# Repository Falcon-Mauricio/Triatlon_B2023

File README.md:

# Triatlon_B2023

### Indice
[PINOUT PCB](#pinout)<br>
[Normas de convivencia de codigo](#normas)<br>
[Organizacion del repositorio y colaboracion](#colab)<br>
[Imagenes](#imag)<br>

## PINOUT PCB

### Kairimi
```
// Motores
#define M2A 22
#define M2B 23
#define M1B 19
#define M1A 21

// Sensores
#define SENSOR_1 13
#define SENSOR_2 27
#define SENSOR_3 26
#define SENSOR_4 25
#define SENSOR_5 34
#define SENSOR_6 35
#define SENSOR_7 32
#define SENSOR_8 33
#define LEFT_CNY 27
#define RIGHT_CNY 25
#define BACK_CNY 26

// Control
#define BUZZER 18
#define PUSH_1 16
#define PUSH_2 17
```

### C5
```
#define SENSOR_1 13 // left side sharp  
#define SENSOR_2 27 // back cny
#define SENSOR_3 26 // right side sharp
#define SENSOR_4 25 // right cny
#define SENSOR_5 34 // left cny
#define SENSOR_6 35 // left sharp
#define SENSOR_7 32 // center sharp
#define SENSOR_8 33 // right sharp

```
<br>

## Normas de convivencia de codigo

* #### 1.  Convencion de nomenclatura:

    | Tipo      | Caso           | Ejemplo      |
    | :-------: |:--------------:|:------------:|
    | constantes| screaming snake|MAX_READING   |
    | variables | snake case     |color_deadline|
    | objetos   | snake case     |left_sharp    |
    | clases    | pascal case    |Motor         |
    | funciones | pascal case    |ReadFloor     |

* #### 2.  Orden del codigo:

    * Importar librerias
    * Definicion pines
    * Definicion de constantes / variables globales
    * Creacion de clases / objetos (hasta terminar la modularizacion)
    * Funciones globales
    * Velocista
    * Sumo radiocontrolado
    * Despejar area
    * Seleccion de modo / setup / loop
    
* #### 3. Legibilidad:

    * Usar define para los numeros aislados
    * Comentarios descriptivos
    * Codigo limpio y ordenado

<br>

## Organizacion del repositorio y colaboracion

### Arbol de carpetas:

```
├───C5
│   ├───3D
│   ├───CODE
│   └───PCB
├───Kairimi
│   ├───3D
│   ├───CODE
│   └───PCB
├───resources
└───shared
    ├───examples
    └───libs
```

* C5: Dedicado a la version C5 (Rodri/Mauri)

* Kairimi: Dedicado a la version Kairimi (Iris/Julian).
* resources: Librerias externas necesarias para correr el codigo
* shared: Archivos compartidos para los dos robots, como librerias dedicadas

### Colaboracion:

Para colaborar es preferible forkear el repositorio, editar lo necesario en el momento y enviar un pull request. Esto para mantener la actualizacion de archivos ordenada y evitar conflictos entre los robots.

Cuando se alcance una version funcional del robot tagerla marcando las diferencias y mejoras respecto a la anterior y tiempos records de pistas.

<br>

## Imagenes 3Ds / PCBs

### KAIRIMI:

### C5:

3d en desarrollo.

# Manolos ahi voy 🤤

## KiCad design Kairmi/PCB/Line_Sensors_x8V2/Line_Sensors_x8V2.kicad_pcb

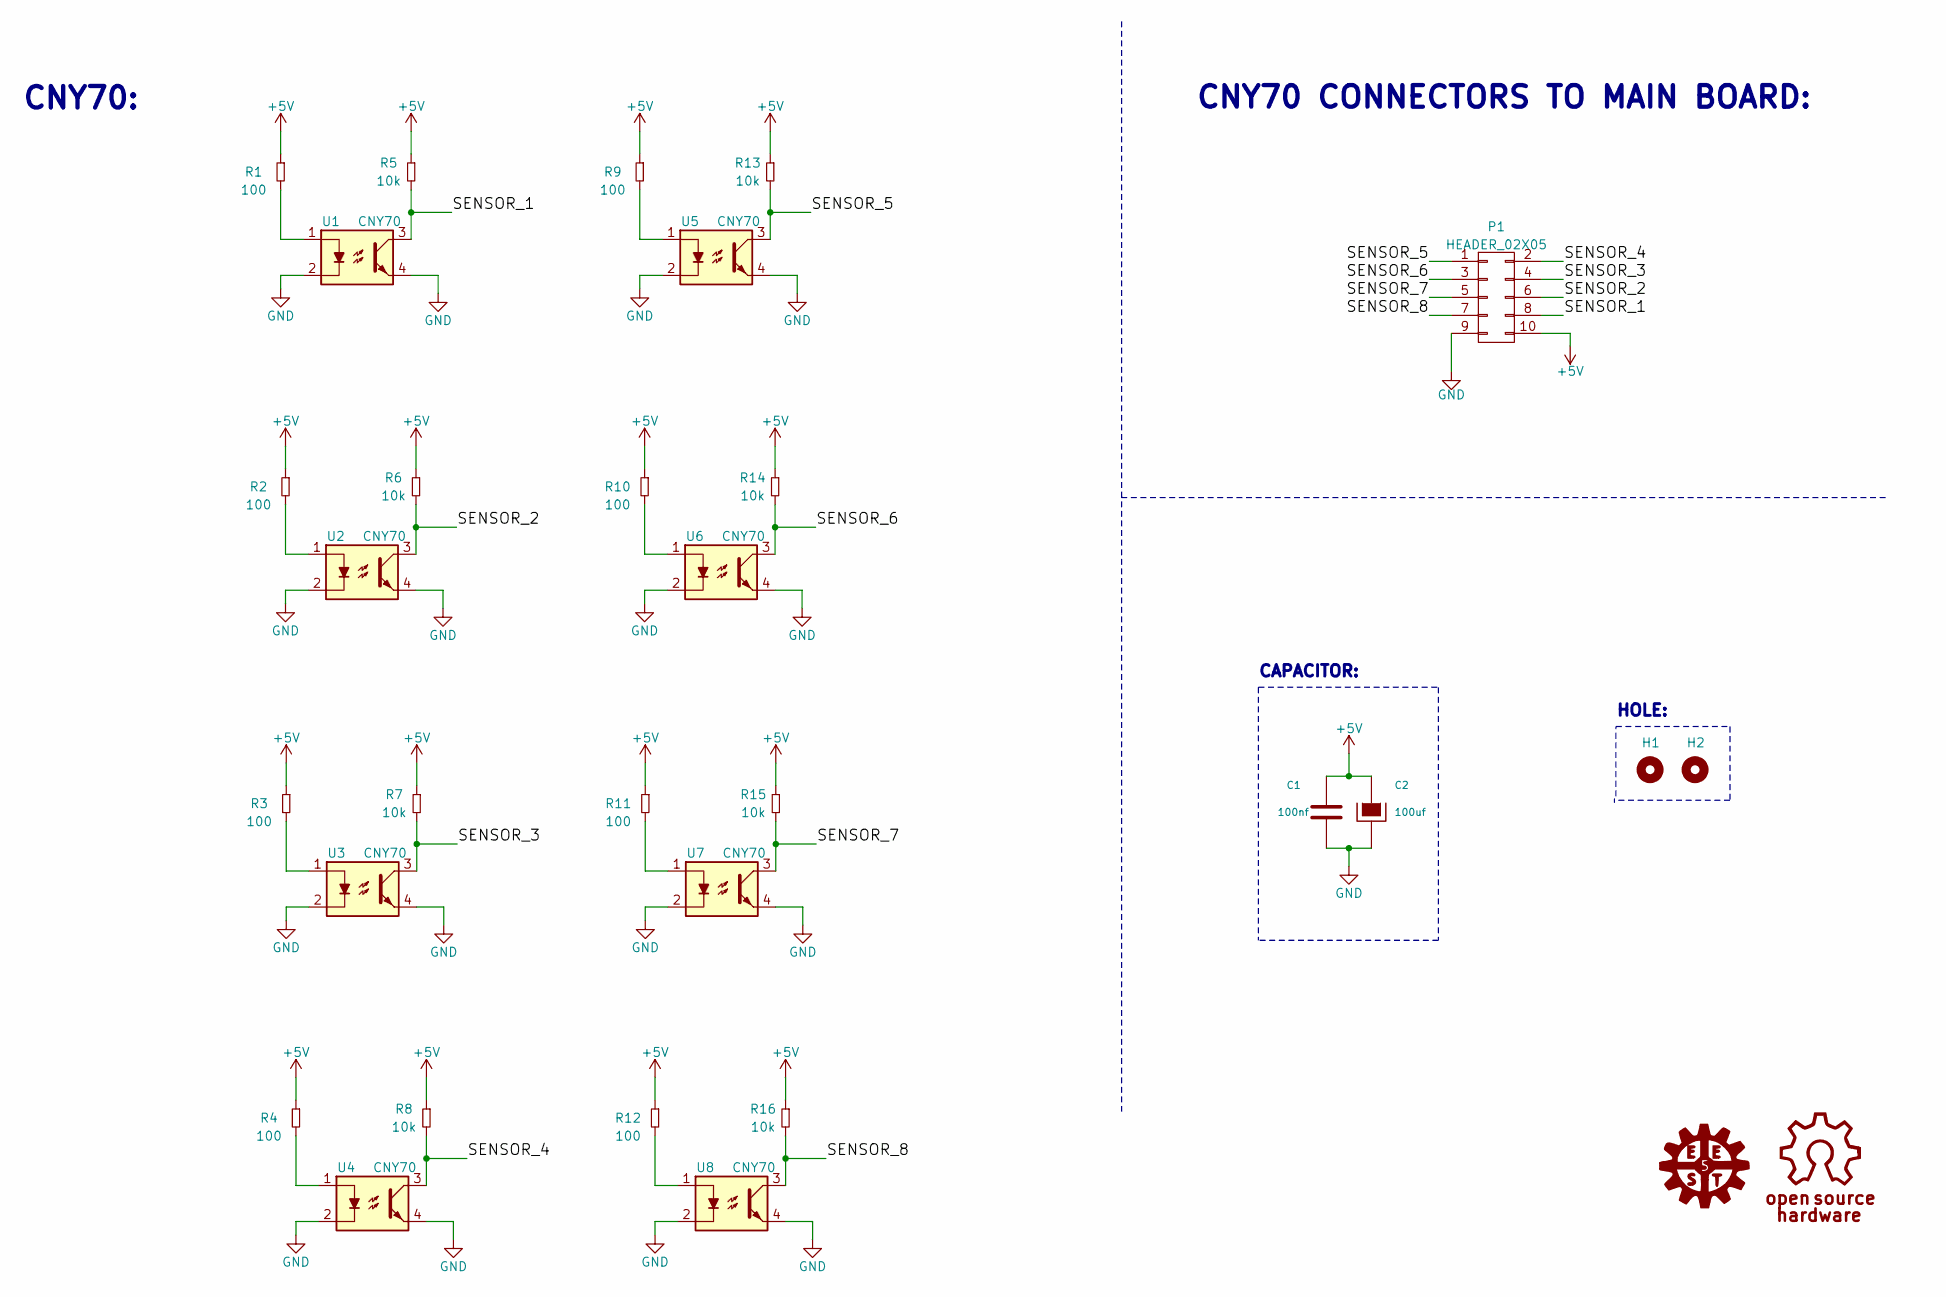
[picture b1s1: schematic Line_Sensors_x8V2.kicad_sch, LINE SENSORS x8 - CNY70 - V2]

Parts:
C1: 100nf; C_0805_2012Metric_Pad1.18x1.45mm_HandSolder
C2: 100uf; C_Radial_D5.0mm_H11.0mm_P2.00mm
H1, H2: HOLE; Separador_M3_5mm
P1: HEADER_02X05; Header_2x05x2.54mm_Vertical
R1, R2, R3, R4, R9, R10, R11, R12: 100; R_1206
R5, R6, R7, R8, R13, R14, R15, R16: 10k; R_1206
U1, U2, U3, U4, U5, U6, U7, U8: CNY70

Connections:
+5V: C1.1, C2.1, P1.10, R1.1, R2.1, R3.1, R4.1, R5.1, R6.1, R7.1, R8.1, R9.1, R10.1, R11.1, R12.1, R13.1, R14.1, R15.1, R16.1
/SENSOR_1: P1.8, R5.2, U1.3
/SENSOR_2: P1.6, R6.2, U2.3
/SENSOR_3: P1.4, R7.2, U3.3
/SENSOR_4: P1.2, R8.2, U4.3
/SENSOR_5: P1.1, R13.2, U5.3
/SENSOR_6: P1.3, R14.2, U6.3
/SENSOR_7: P1.5, R15.2, U7.3
/SENSOR_8: P1.7, R16.2, U8.3
GND: C1.2, C2.2, P1.9, U1.2, U1.4, U2.2, U2.4, U3.2, U3.4, U4.2, U4.4, U5.2, U5.4, U6.2, U6.4, U7.2, U7.4, U8.2, U8.4
unnamed: R1.2, U1.1
unnamed: R2.2, U2.1
unnamed: R3.2, U3.1
unnamed: R4.2, U4.1
unnamed: R9.2, U5.1
unnamed: R10.2, U6.1
unnamed: R11.2, U7.1
unnamed: R12.2, U8.1

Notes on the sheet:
CNY70 CONNECTORS TO MAIN BOARD:
CAPACITOR:
CNY70:
HOLE:

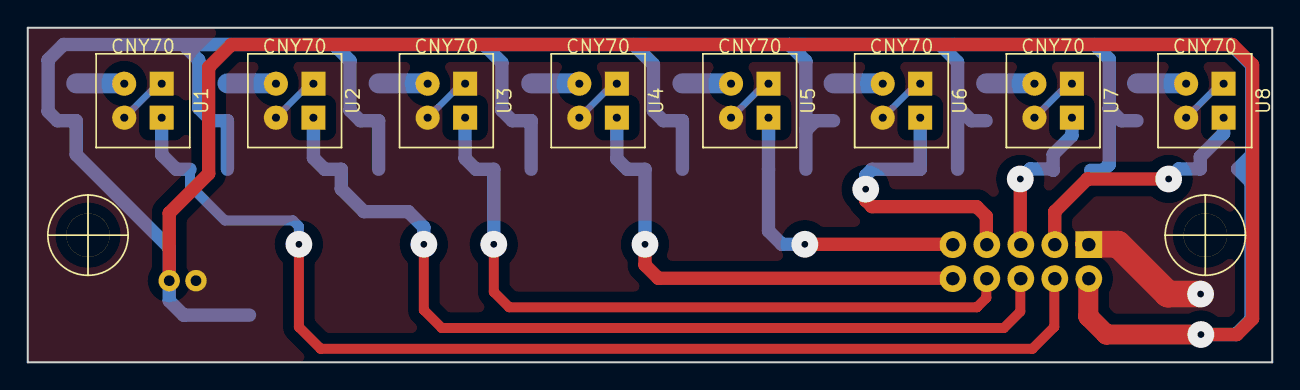
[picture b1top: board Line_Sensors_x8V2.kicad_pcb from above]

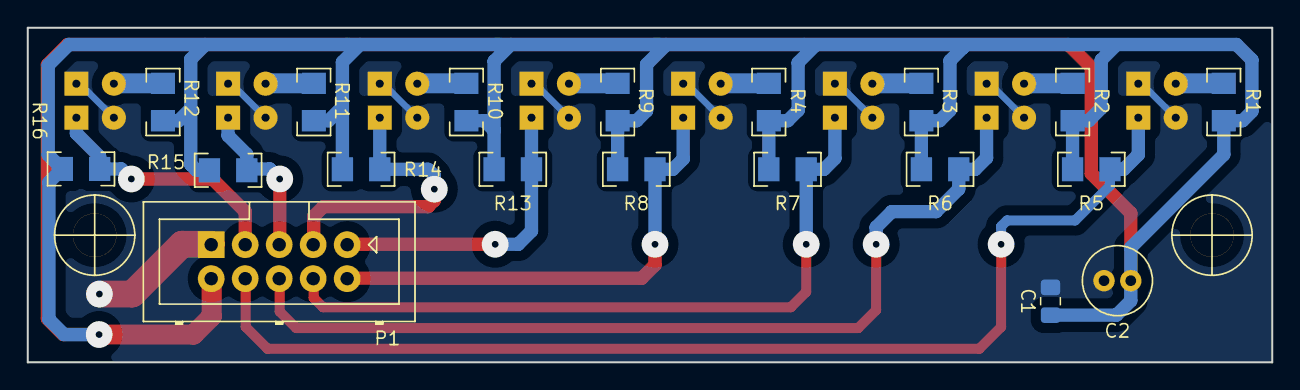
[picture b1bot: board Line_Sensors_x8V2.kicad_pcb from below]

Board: 2 copper layers, 93.0 x 25.0 mm, 29 parts (21 on the bottom side), 18 nets.

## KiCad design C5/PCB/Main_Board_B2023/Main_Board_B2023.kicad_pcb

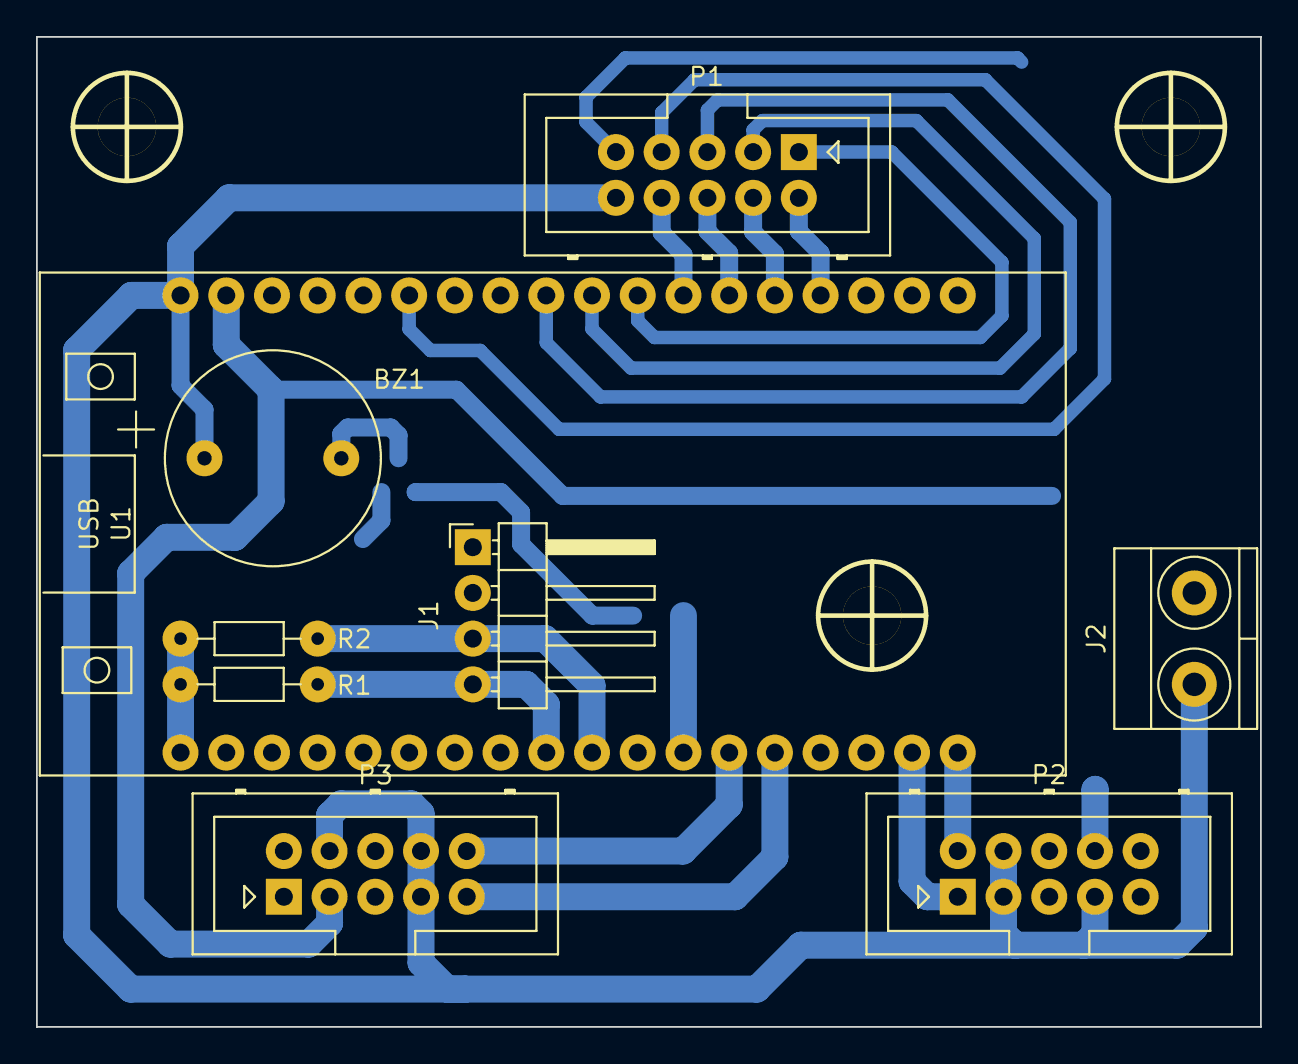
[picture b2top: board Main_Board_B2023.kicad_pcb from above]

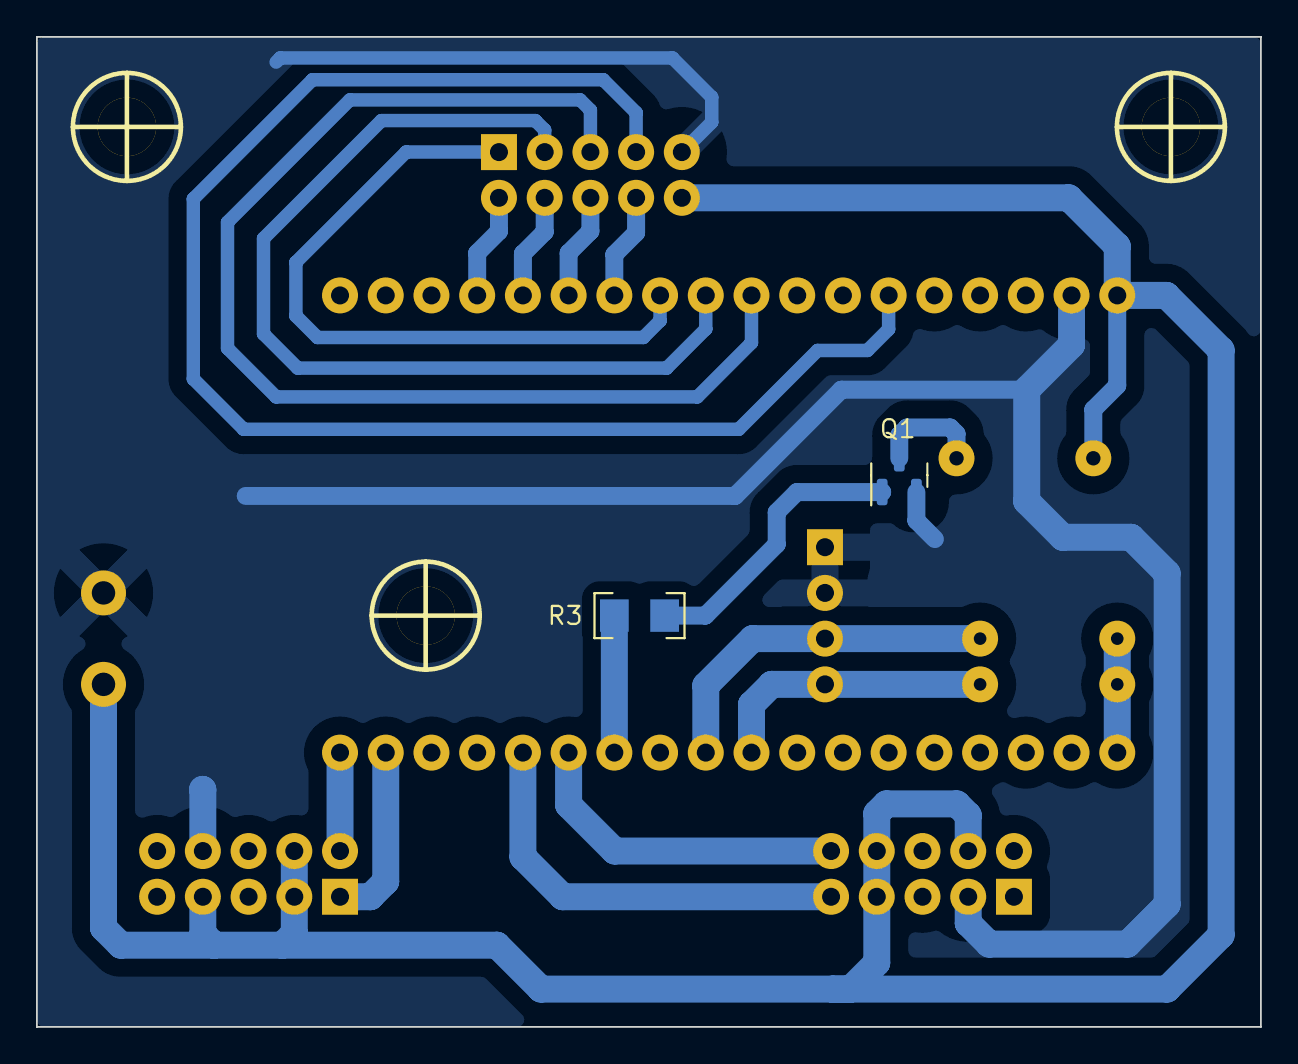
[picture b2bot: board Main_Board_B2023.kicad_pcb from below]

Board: 2 copper layers, 68.0 x 55.0 mm, 14 parts (2 on the bottom side), 20 nets.

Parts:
BZ1: Buzzer; Buzzer_12mm
H1, H2, H3: Mounting_Hole; Separador_M3_5mm
J1: Conn_01x04_Pin; PinHeader_1x04_P2.54mm_Horizontal
J2: TB_1X2; BORNERA2_AZUL
P1, P2, P3: HEADER_02X05; Header_2x05x2.54mm_Vertical
Q1: 2N7002; SOT-23
R1, R2: 4K7; R_Axial_DIN0204_L3.6mm_D1.6mm_P7.62mm_Horizontal
R3: 10K; R_1206
U1: ESP32_DevKit_V1_DOIT; ESP32_DEVKIT_V1_DOIT

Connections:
+3V3: R1.1, R2.1, U1.19 (3V3)
+5V: BZ1.1 (-), J2.1, P1.10, P2.3, P2.4, P2.7, P3.4, P3.7, P3.8, U1.18 (VIN)
/BUZZER: R3.2, U1.30 (IO18)
/M1A: P2.1, U1.35 (IO22)
/M1B: P2.2, U1.36 (IO23)
/M2A: P3.10, U1.31 (IO19)
/M2B: P3.9, U1.32 (IO21)
/PUSH_1: J1.4, R1.2, U1.27 (RX2)
/PUSH_2: J1.3, R2.2, U1.28 (TX2)
/SENSOR_1: P1.2, U1.4 (IO34)
/SENSOR_2: P1.4, U1.5 (IO35)
/SENSOR_3: P1.6, U1.6 (IO32)
/SENSOR_4: P1.8, U1.7 (IO33)
/SENSOR_5: P1.1, U1.8 (IO25)
/SENSOR_6: P1.3, U1.9 (IO26)
/SENSOR_7: P1.5, U1.10 (IO27)
/SENSOR_8: P1.7, U1.13 (IO13)
GND: J1.1, J1.2, J2.2, P1.9, P2.8, P3.3, Q1.2 (S), U1.17 (GND)
unnamed: BZ1.2 (+), Q1.3 (D)
unnamed: Q1.1 (G), R3.1

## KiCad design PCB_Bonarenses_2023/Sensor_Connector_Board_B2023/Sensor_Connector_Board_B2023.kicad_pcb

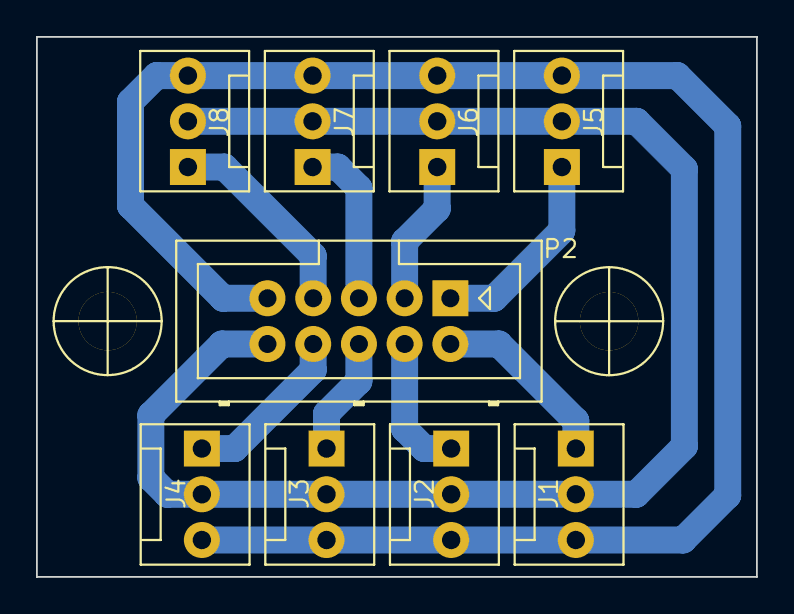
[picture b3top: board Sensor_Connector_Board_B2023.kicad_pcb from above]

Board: 2 copper layers, 40.0 x 30.0 mm, 11 parts (0 on the bottom side), 10 nets.

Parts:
H3, H4: Mounting_Hole; Separador_M3_5mm
J1, J2, J3, J4, J5, J6, J7, J8: Conn; FanPinHeader_1x03_P2.54mm_Vertical
P2: HEADER_02X05; Header_2x05x2.54mm_Vertical

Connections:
+5V: J1.2, J2.2, J3.2, J4.2, J5.2, J6.2, J7.2, J8.2, P2.10
/INP_1: J1.1, P2.2
/INP_2: J2.1, P2.4
/INP_3: J3.1, P2.6
/INP_4: J4.1, P2.8
/INP_5: J5.1, P2.1
/INP_6: J6.1, P2.3
/INP_7: J7.1, P2.5
/INP_8: J8.1, P2.7
GND: J1.3, J2.3, J3.3, J4.3, J5.3, J6.3, J7.3, J8.3, P2.9

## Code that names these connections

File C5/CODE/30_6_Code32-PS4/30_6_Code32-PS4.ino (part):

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
#define DEBUG 1
// Motores
#define M2A 22
#define M2B 23
#define M1B 19
#define M1A 21

// Sensores
#define SENSOR_1 13
#define SENSOR_2 27
#define SENSOR_3 26
#define SENSOR_4 25
#define SENSOR_5 34
#define SENSOR_6 35
#define SENSOR_7 32
#define SENSOR_8 33
#define left_CNY 27
#define right_CNY 25

int Cny70_pins[] = { SENSOR_1, SENSOR_2, SENSOR_3, SENSOR_4, SENSOR_5, SENSOR_6, SENSOR_7, SENSOR_8 };

#define CNY70_CANT 8

// Control
#define BUZZER 18
#define PUSH_1 16
#define PUSH_2 17

// Constantes

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  int pin;

public:
  Buzzer(int pin);
  void Use(int duration);
  void Beep(int n, int duration);
};

Buzzer::Buzzer(int pin_in) {
  pin = pin_in;
  pinMode(pin, OUTPUT);
  digitalWrite(pin, LOW);
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  int values_read[CNY70_CANT];
  int max_value_read[CNY70_CANT];
  int min_value_read[CNY70_CANT];
  int Cny70_pins[8] = { SENSOR_1, SENSOR_2, SENSOR_3, SENSOR_4, SENSOR_5, SENSOR_6, SENSOR_7, SENSOR_8 };

public:
  PID();
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
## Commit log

2023-04-26 Fueron agregados los archivos 3D del robot junto a los diseños PCB y el codigo del menu
2023-05-06 Elimine Backups incesesarios de los PCB's y agregue el codigo de pruebas de motores
2023-05-14 Arregle el Diseño 3D del techo
2023-07-02 Creacion de los Codigos de Velocista, Quita obstaculos y SumoRC
2023-07-18 Nuevo Diseño de la tapa y arreglo del soporte del sensor del medio
2023-07-21 Añadido codigo 4/7 y Motor_class
2023-08-06 Organize folders
2023-08-06 Add C5 folders
2023-08-06 Add shared for common files
2023-08-06 Create Main.ino file
2023-08-06 Add necessary resources
2023-08-07 Add calibrate area cleaner
2023-08-09 Add AC calibrate & Debug mode_selection
2023-08-28 Debuging
2023-08-30 Add and configure files for libs separation
2023-09-04 Move motor module to main
2023-09-04 Add pin verification script
2023-09-04 Add saw right case & Clean code
2023-09-06 Update area_cleaner functionalities
2023-09-06 Update line_follower functionalities
2023-09-06 Add c5 CODE files
2023-09-08 Update area_cleaner & line_follower functionalities
2023-09-13 Adjust line_follower variables
2023-09-16 Add area_cleaner telemetry
2023-09-16 Line_follower 12seg, Area_cleaner 30seg
2023-09-17 1ra version MDQ
2023-09-17 chore: se agrego llaves
2023-09-18 chore: se agrego enum para los swich case y el codigo de navarimi
2023-09-18 chore: fix print mode
2023-09-18 chore: cambie variables globales a variables locales
2023-09-18 chore: fix rebote
2023-09-18 DA 23seg
2023-09-18 More DA velocity
2023-09-18 Debug back cny rebound
2023-09-18 SOMOS CAMPEONES
